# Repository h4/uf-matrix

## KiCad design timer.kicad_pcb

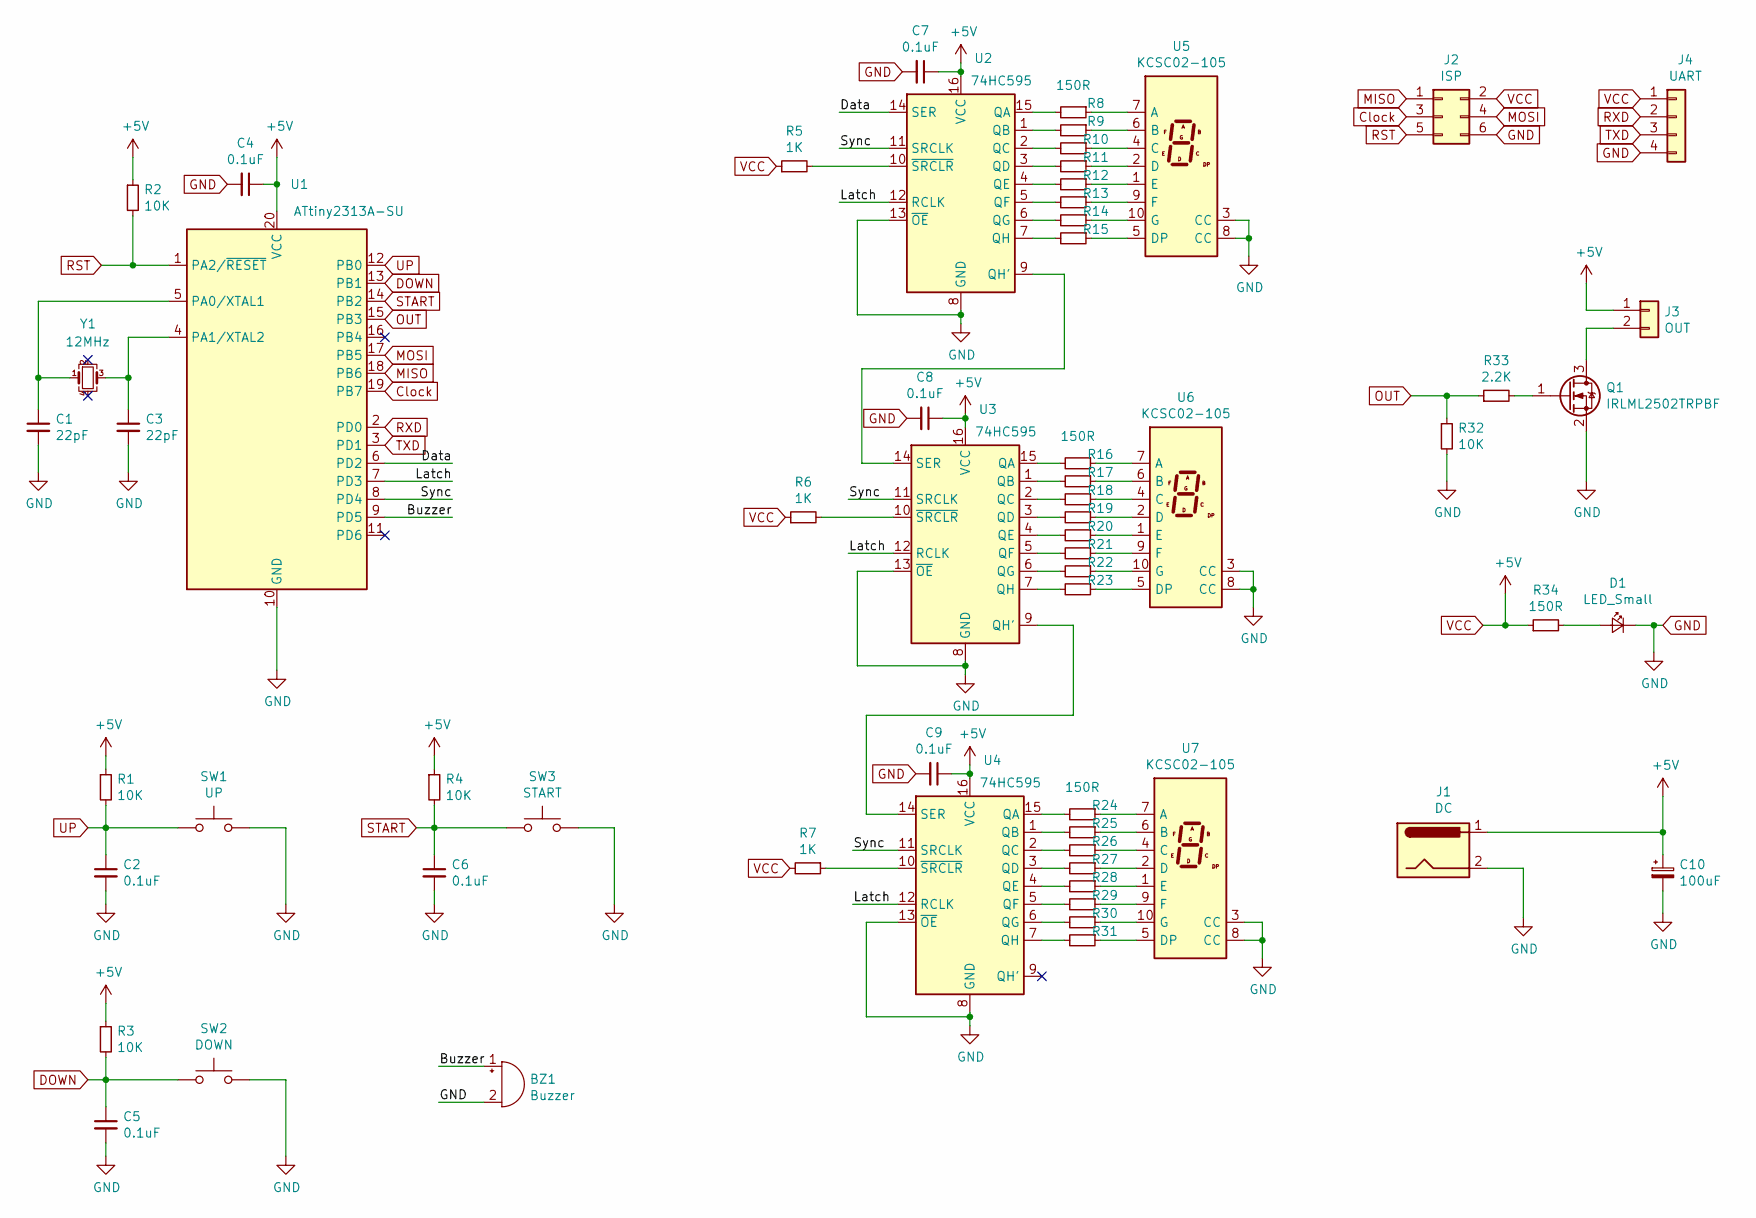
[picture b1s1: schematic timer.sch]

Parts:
BZ1: Buzzer; Buzzer_12x9.5RM7.6
C1, C3: 22pF; C_0805_2012Metric_Pad1.15x1.40mm_HandSolder
C2, C4, C5, C6, C7, C8, C9: 0.1uF; C_0805_2012Metric_Pad1.15x1.40mm_HandSolder
C10: 100uF; CP_EIA-7343-31_Kemet-D_Pad2.25x2.55mm_HandSolder
D1: LED_Small; LED_0805_2012Metric_Pad1.15x1.40mm_HandSolder
J1: DC; BarrelJack_Horizontal
J2: ISP; PinHeader_2x03_P2.54mm_Vertical
J3: OUT; TerminalBlock_TE_282834-2_1x02_P2.54mm_Horizontal
J4: UART; PinHeader_1x04_P2.54mm_Vertical
Q1: IRLML2502TRPBF; SOT-23
R1, R2, R3, R4, R32: 10K; R_0805_2012Metric_Pad1.15x1.40mm_HandSolder
R5, R6, R7: 1K; R_0805_2012Metric_Pad1.15x1.40mm_HandSolder
R8, R16, R24, R34: 150R; R_0805_2012Metric_Pad1.15x1.40mm_HandSolder
R9, R10, R11, R12, R13, R14, R15, R17, R18, R19, R20, R21, R22, R23, R25, R26, R27, R28, R29, R30, R31: R_Small; R_0805_2012Metric_Pad1.15x1.40mm_HandSolder
R33: 2.2K; R_0805_2012Metric_Pad1.15x1.40mm_HandSolder
SW1: UP; SW_SPST_EVPBF
SW2: DOWN; SW_SPST_EVPBF
SW3: START; SW_SPST_EVPBF
U1: ATtiny2313A-SU; SOIC-20W_7.5x12.8mm_P1.27mm
U2, U3, U4: 74HC595; SOIC-16_3.9x9.9mm_P1.27mm
U5, U6, U7: KCSC02-105
Y1: 12MHz; Crystal_SMD_SeikoEpson_FA238V-4Pin_3.2x2.5mm_HandSoldering

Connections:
/Buzzer: BZ1.1 (-), U1.9 (PD5)
/Data: U1.6 (PD2), U2.14 (SER)
/Latch: U1.7 (PD3), U2.12 (RCLK), U3.12 (RCLK), U4.12 (RCLK)
/Sync: U1.8 (PD4), U2.11 (SRCLK), U3.11 (SRCLK), U4.11 (SRCLK)
Clock: J2.3, U1.19 (PB7)
DOWN: C5.1, R3.2, SW2.1, U1.13 (PB1)
GND: BZ1.2 (+), C1.2, C2.2, C3.2, C4.2, C5.2, C6.2, C7.2, C8.2, C9.2, C10.2, D1.1 (K), J1.2, J2.6, J4.4, Q1.2 (S), R32.2, SW1.2, SW2.2, SW3.2, U1.10 (GND), U2.8 (GND), U2.13 (~OE), U3.8 (GND), U3.13 (~OE), U4.8 (GND), U4.13 (~OE), U5.3 (CC), U5.8 (CC), U6.3 (CC), U6.8 (CC), U7.3 (CC), U7.8 (CC)
MISO: J2.1, U1.18 (PB6)
MOSI: J2.4, U1.17 (PB5)
unnamed: C1.1, U1.5 (PA0/XTAL1), Y1.1
unnamed: C3.1, U1.4 (PA1/XTAL2), Y1.3
unnamed: D1.2 (A), R34.2
unnamed: J3.2, Q1.3 (D)
unnamed: Q1.1 (G), R33.2
unnamed: R5.2, U2.10 (~SRCLR)
unnamed: R6.2, U3.10 (~SRCLR)
unnamed: R7.1, U4.10 (~SRCLR)
unnamed: R8.1, U5.7 (A)
unnamed: R8.2, U2.15 (QA)
unnamed: R9.1, U5.6 (B)
unnamed: R9.2, U2.1 (QB)
unnamed: R10.1, U5.4 (C)
unnamed: R10.2, U2.2 (QC)
unnamed: R11.1, U5.2 (D)
unnamed: R11.2, U2.3 (QD)
unnamed: R12.1, U5.1 (E)
unnamed: R12.2, U2.4 (QE)
unnamed: R13.1, U5.9 (F)
unnamed: R13.2, U2.5 (QF)
unnamed: R14.1, U5.10 (G)
unnamed: R14.2, U2.6 (QG)
unnamed: R15.1, U5.5 (DP)
unnamed: R15.2, U2.7 (QH)
unnamed: R16.1, U6.7 (A)
unnamed: R16.2, U3.15 (QA)
unnamed: R17.1, U6.6 (B)
unnamed: R17.2, U3.1 (QB)
unnamed: R18.1, U6.4 (C)
unnamed: R18.2, U3.2 (QC)
unnamed: R19.1, U6.2 (D)
unnamed: R19.2, U3.3 (QD)
unnamed: R20.1, U6.1 (E)
unnamed: R20.2, U3.4 (QE)
unnamed: R21.1, U6.9 (F)
unnamed: R21.2, U3.5 (QF)
unnamed: R22.1, U6.10 (G)
unnamed: R22.2, U3.6 (QG)
unnamed: R23.1, U6.5 (DP)
unnamed: R23.2, U3.7 (QH)
unnamed: R24.1, U7.7 (A)
unnamed: R24.2, U4.15 (QA)
unnamed: R25.1, U7.6 (B)
unnamed: R25.2, U4.1 (QB)
unnamed: R26.1, U7.4 (C)
unnamed: R26.2, U4.2 (QC)
unnamed: R27.1, U7.2 (D)
unnamed: R27.2, U4.3 (QD)
unnamed: R28.1, U7.1 (E)
unnamed: R28.2, U4.4 (QE)
unnamed: R29.1, U7.9 (F)
unnamed: R29.2, U4.5 (QF)
unnamed: R30.1, U7.10 (G)
unnamed: R30.2, U4.6 (QG)
unnamed: R31.1, U7.5 (DP)
unnamed: R31.2, U4.7 (QH)
unnamed: U2.9 (QH'), U3.14 (SER)
unnamed: U3.9 (QH'), U4.14 (SER)
OUT: R32.1, R33.1, U1.15 (PB3)
RST: J2.5, R2.2, U1.1 (PA2/~RESET)
RXD: J4.2, U1.2 (PD0)
START: C6.1, R4.2, SW3.1, U1.14 (PB2)
TXD: J4.3, U1.3 (PD1)
UP: C2.1, R1.2, SW1.1, U1.12 (PB0)
VCC: C4.1, C7.1, C8.1, C9.1, C10.1, J1.1, J2.2, J3.1, J4.1, R1.1, R2.1, R3.1, R4.1, R5.1, R6.1, R7.2, R34.1, U1.20 (VCC), U2.16 (VCC), U3.16 (VCC), U4.16 (VCC)

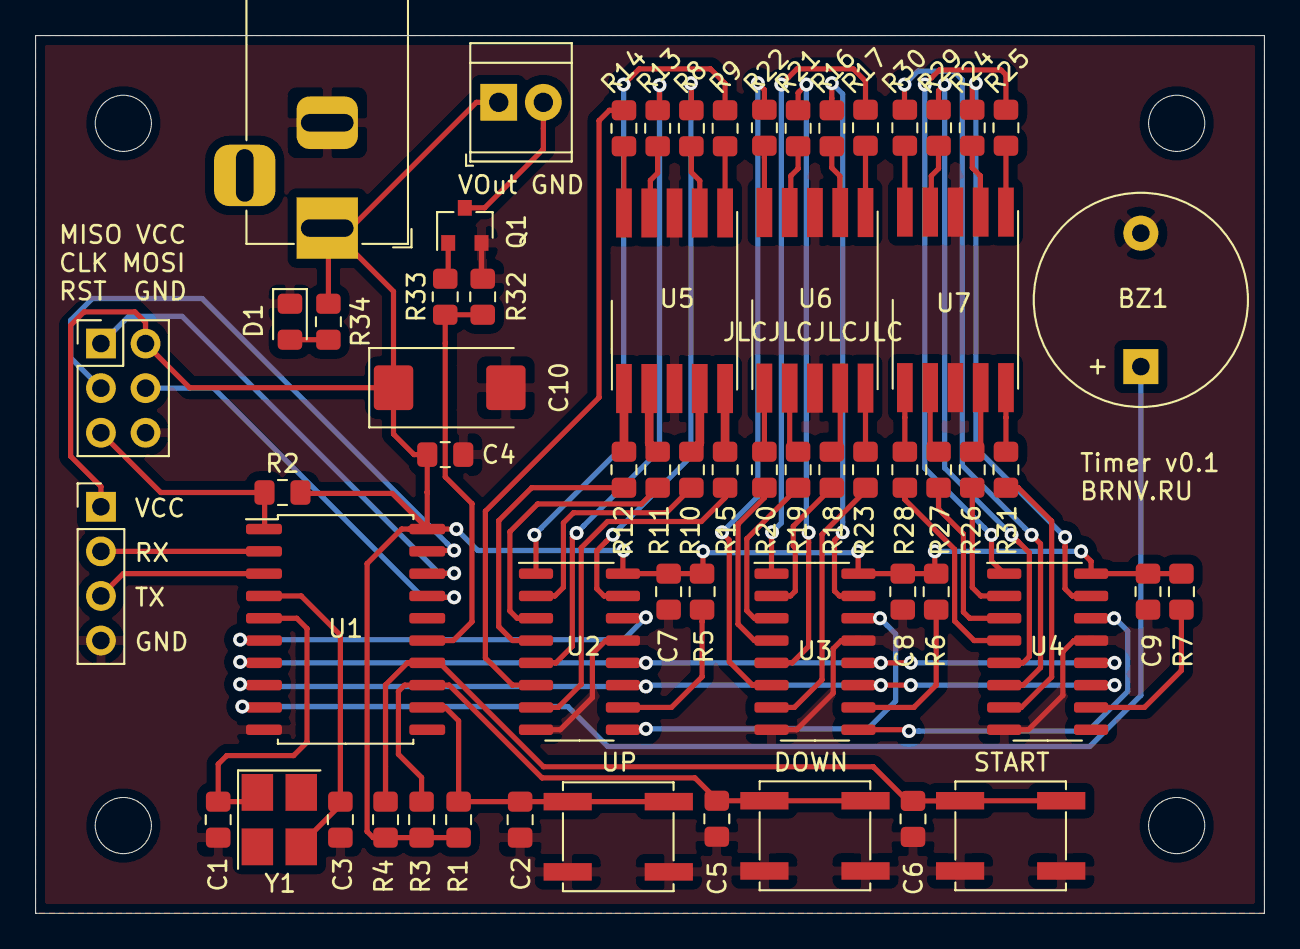
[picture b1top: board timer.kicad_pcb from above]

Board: 2 copper layers, 70.0 x 50.0 mm, 62 parts (0 on the bottom side), 74 nets.

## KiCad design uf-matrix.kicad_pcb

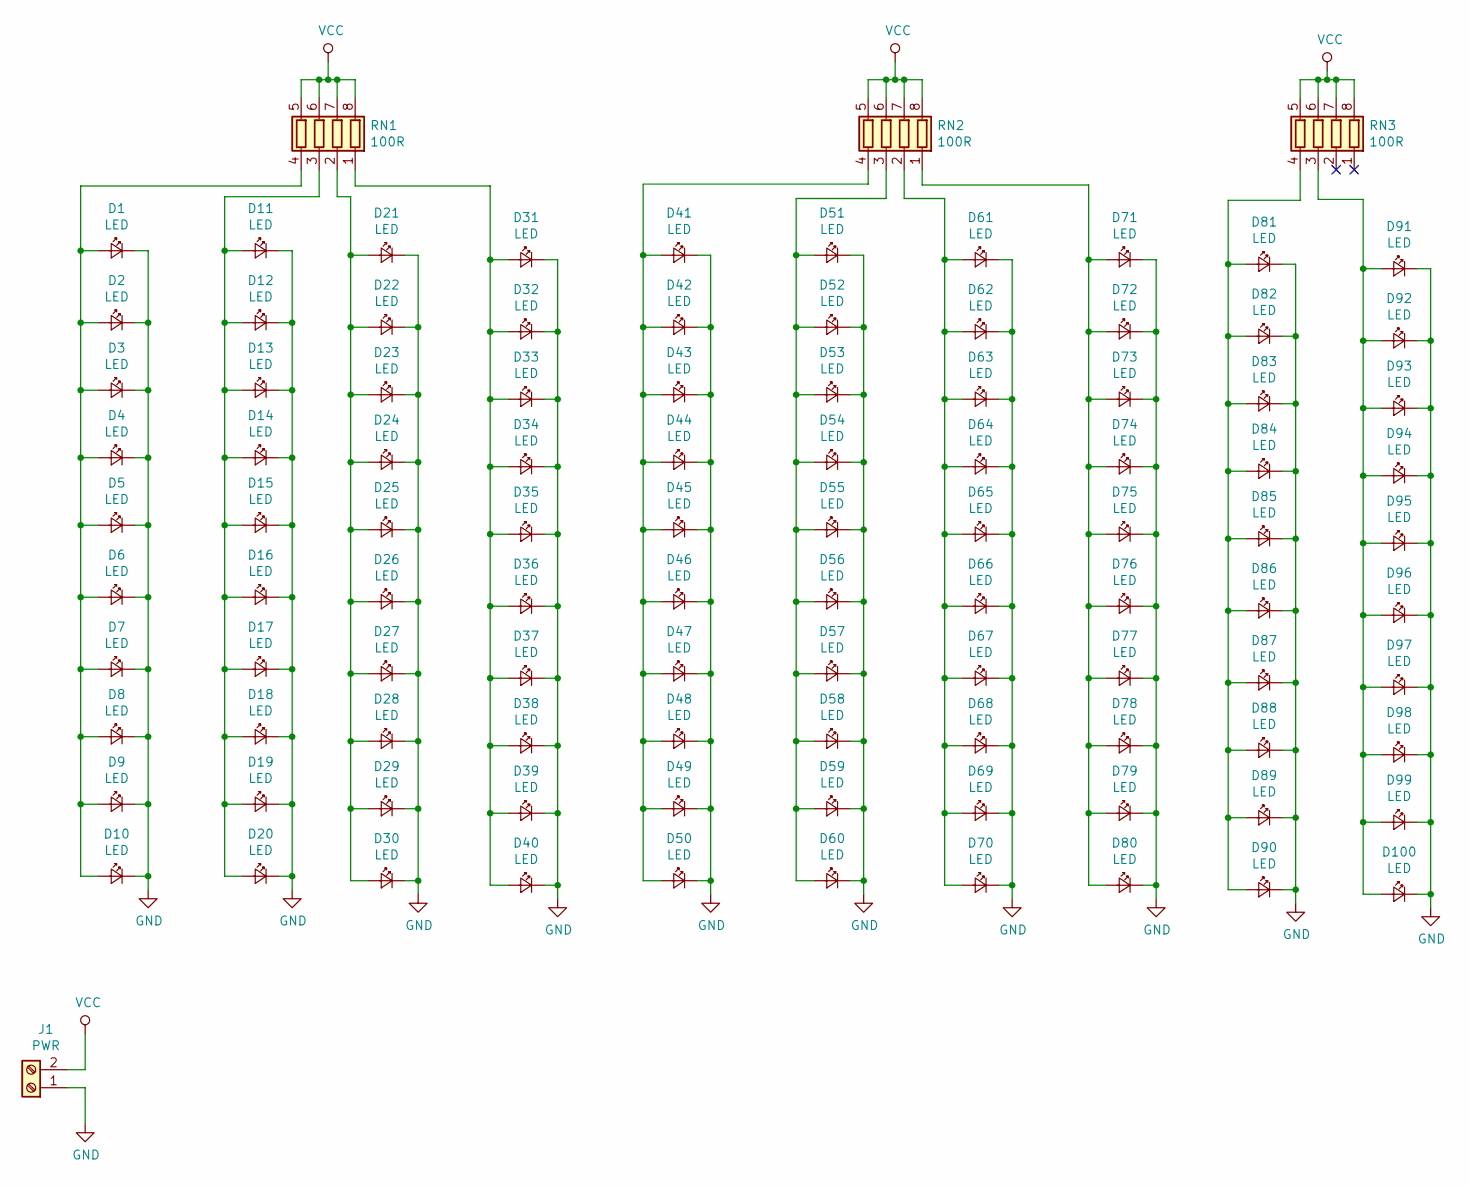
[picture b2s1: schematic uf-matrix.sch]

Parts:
D1, D2, D3, D4, D5, D6, D7, D8, D9, D10, D11, D12, D13, D14, D15, D16, D17, D18, D19, D20, D21, D22, D23, D24, D25, D26, D27, D28, D29, D30, D31, D32, D33, D34, D35, D36, D37, D38, D39, D40, D41, D42, D43, D44, D45, D46, D47, D48, D49, D50, D51, D52, D53, D54, D55, D56, D57, D58, D59, D60, D61, D62, D63, D64, D65, D66, D67, D68, D69, D70, D71, D72, D73, D74, D75, D76, D77, D78, D79, D80, D81, D82, D83, D84, D85, D86, D87, D88, D89, D90, D91, D92, D93, D94, D95, D96, D97, D98, D99, D100: LED; LED_1210_3225Metric_Pad1.42x2.65mm_HandSolder
J1: PWR; TerminalBlock_bornier-2_P5.08mm
RN1, RN2, RN3: 100R; R_Array_Convex_4x0603

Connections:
GND: D1.1 (K), D2.1 (K), D3.1 (K), D4.1 (K), D5.1 (K), D6.1 (K), D7.1 (K), D8.1 (K), D9.1 (K), D10.1 (K), D11.1 (K), D12.1 (K), D13.1 (K), D14.1 (K), D15.1 (K), D16.1 (K), D17.1 (K), D18.1 (K), D19.1 (K), D20.1 (K), D21.1 (K), D22.1 (K), D23.1 (K), D24.1 (K), D25.1 (K), D26.1 (K), D27.1 (K), D28.1 (K), D29.1 (K), D30.1 (K), D31.1 (K), D32.1 (K), D33.1 (K), D34.1 (K), D35.1 (K), D36.1 (K), D37.1 (K), D38.1 (K), D39.1 (K), D40.1 (K), D41.1 (K), D42.1 (K), D43.1 (K), D44.1 (K), D45.1 (K), D46.1 (K), D47.1 (K), D48.1 (K), D49.1 (K), D50.1 (K), D51.1 (K), D52.1 (K), D53.1 (K), D54.1 (K), D55.1 (K), D56.1 (K), D57.1 (K), D58.1 (K), D59.1 (K), D60.1 (K), D61.1 (K), D62.1 (K), D63.1 (K), D64.1 (K), D65.1 (K), D66.1 (K), D67.1 (K), D68.1 (K), D69.1 (K), D70.1 (K), D71.1 (K), D72.1 (K), D73.1 (K), D74.1 (K), D75.1 (K), D76.1 (K), D77.1 (K), D78.1 (K), D79.1 (K), D80.1 (K), D81.1 (K), D82.1 (K), D83.1 (K), D84.1 (K), D85.1 (K), D86.1 (K), D87.1 (K), D88.1 (K), D89.1 (K), D90.1 (K), D91.1 (K), D92.1 (K), D93.1 (K), D94.1 (K), D95.1 (K), D96.1 (K), D97.1 (K), D98.1 (K), D99.1 (K), D100.1 (K), J1.1
unnamed: D1.2 (A), D2.2 (A), D3.2 (A), D4.2 (A), D5.2 (A), D6.2 (A), D7.2 (A), D8.2 (A), D9.2 (A), D10.2 (A), RN1.4 (R4.1)
unnamed: D11.2 (A), D12.2 (A), D13.2 (A), D14.2 (A), D15.2 (A), D16.2 (A), D17.2 (A), D18.2 (A), D19.2 (A), D20.2 (A), RN1.3 (R3.1)
unnamed: D21.2 (A), D22.2 (A), D23.2 (A), D24.2 (A), D25.2 (A), D26.2 (A), D27.2 (A), D28.2 (A), D29.2 (A), D30.2 (A), RN1.2 (R2.1)
unnamed: D31.2 (A), D32.2 (A), D33.2 (A), D34.2 (A), D35.2 (A), D36.2 (A), D37.2 (A), D38.2 (A), D39.2 (A), D40.2 (A), RN1.1 (R1.1)
unnamed: D41.2 (A), D42.2 (A), D43.2 (A), D44.2 (A), D45.2 (A), D46.2 (A), D47.2 (A), D48.2 (A), D49.2 (A), D50.2 (A), RN2.4 (R4.1)
unnamed: D51.2 (A), D52.2 (A), D53.2 (A), D54.2 (A), D55.2 (A), D56.2 (A), D57.2 (A), D58.2 (A), D59.2 (A), D60.2 (A), RN2.3 (R3.1)
unnamed: D61.2 (A), D62.2 (A), D63.2 (A), D64.2 (A), D65.2 (A), D66.2 (A), D67.2 (A), D68.2 (A), D69.2 (A), D70.2 (A), RN2.2 (R2.1)
unnamed: D71.2 (A), D72.2 (A), D73.2 (A), D74.2 (A), D75.2 (A), D76.2 (A), D77.2 (A), D78.2 (A), D79.2 (A), D80.2 (A), RN2.1 (R1.1)
unnamed: D81.2 (A), D82.2 (A), D83.2 (A), D84.2 (A), D85.2 (A), D86.2 (A), D87.2 (A), D88.2 (A), D89.2 (A), D90.2 (A), RN3.4 (R4.1)
unnamed: D91.2 (A), D92.2 (A), D93.2 (A), D94.2 (A), D95.2 (A), D96.2 (A), D97.2 (A), D98.2 (A), D99.2 (A), D100.2 (A), RN3.3 (R3.1)
VCC: J1.2, RN1.5 (R4.2), RN1.6 (R3.2), RN1.7 (R2.2), RN1.8 (R1.2), RN2.5 (R4.2), RN2.6 (R3.2), RN2.7 (R2.2), RN2.8 (R1.2), RN3.5 (R4.2), RN3.6 (R3.2), RN3.7 (R2.2), RN3.8 (R1.2)

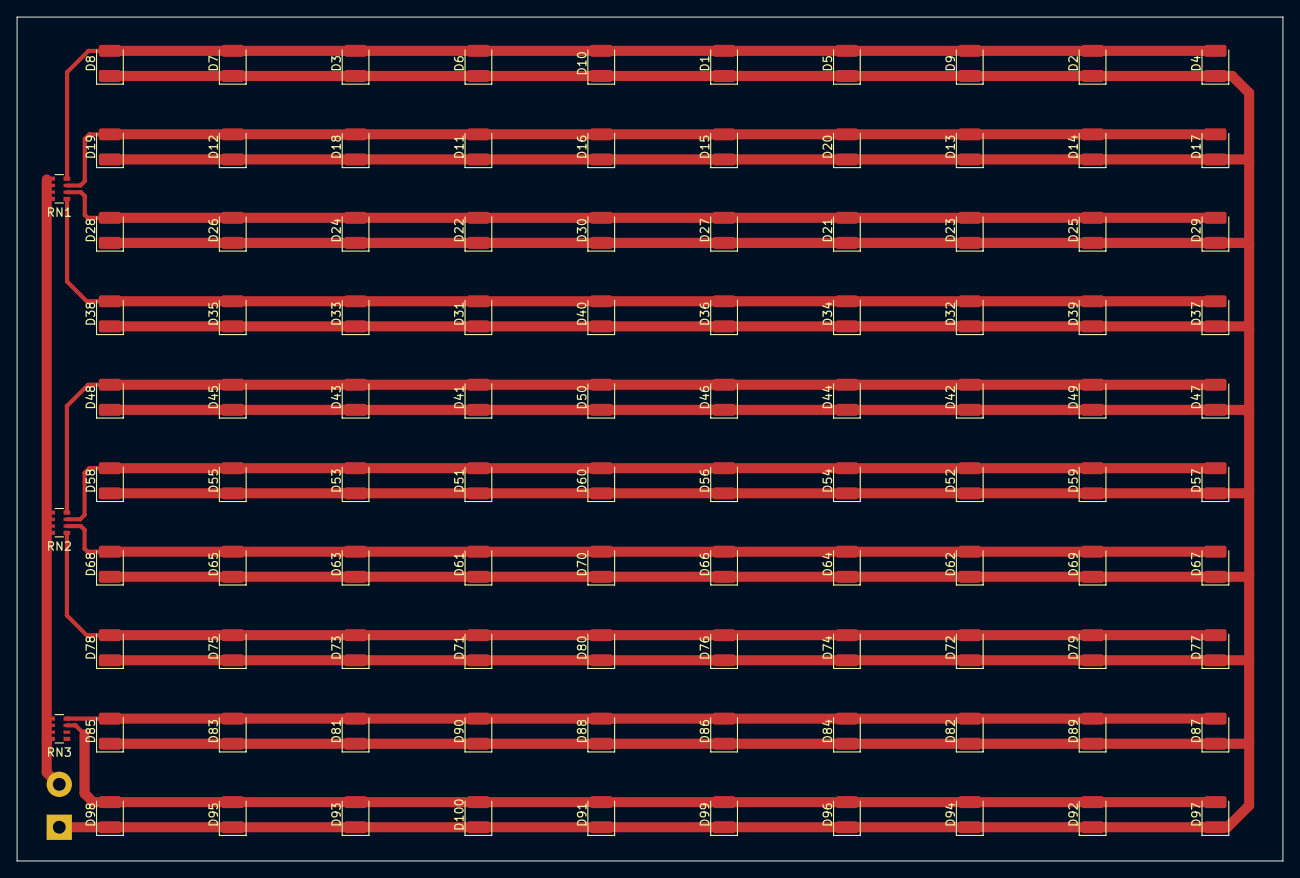
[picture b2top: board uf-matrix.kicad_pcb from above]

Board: 2 copper layers, 150.0 x 100.0 mm, 104 parts (1 on the bottom side), 12 nets.

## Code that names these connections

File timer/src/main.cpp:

#include <Arduino.h>
#include <avr/io.h>
#include <util/delay.h>

#define OUT_PIN PB3
#define DATA_PIN PD2
#define LATCH_PIN PD3
#define CLOCK_PIN PD4
#define BUZZER_PIN PD5

#define UP_PIN PB0
#define DOWN_PIN PB1
#define START_PIN PB2

bool state = false;
unsigned int time = 45;
unsigned int elapsed;
bool timer_enabled = false;

unsigned int NUMS_MAP[10] = {
    //abcdefg.
    0b00111111,
    0b00000110,
    0b01011011,
    0b01001111,
    0b01100110,
    0b01101101,
    0b01111101,
    0b00000111,
    0b01111111,
    0b01101111
};

void pinHigh(volatile uint8_t *port, int pin) {
  *port |= (1 << pin);
}

void pinLow(volatile uint8_t *port, int pin) {
  *port &= ~(1 << pin);
}

void init_led() {
  DDRD |= ((1 << DATA_PIN) | (1 << CLOCK_PIN) | (1 << LATCH_PIN));
}

void init_buzzer() {
  DDRD |= (1 << BUZZER_PIN);
  // Configure counter for PWM. Enable PWM, set fast PWM, use external crystal
  TCCR0A = (1 << COM0A1) | (1 << COM0B1) | (1 << WGM01) | (1 << WGM00) | (1 << CS02) | (1 << CS01) | (1 << CS00);
}

void init_buttons() {
  DDRB &= (~(1 << UP_PIN) & ~(1 << DOWN_PIN) & ~(1 << START_PIN));
  PORTB |= ((1 << START_PIN) | (1 << DOWN_PIN) | (1 << START_PIN));
}

void init_out() {
  DDRB |= (1 << OUT_PIN);
  PORTB &= ~(1 << OUT_PIN);
}

void setup() {
  PORTB = 0b00000000;
  
  init_buttons();
  init_led();
  init_buzzer();
  init_out();
}

void put_byte(int n, bool invert) {
  int bits = NUMS_MAP[n];
  if (invert) {
    bits = ~bits;
  }

  for (int i=0; i < 8; i++) {
    //Output the data on DS line according to the
    //Value of MSB
    if (bits & 0b10000000) {
        //MSB is 1 so output high
        pinHigh(&PORTD, DATA_PIN);
    } else {
        //MSB is 0 so output high
        pinLow(&PORTD, DATA_PIN);
    }
    pinHigh(&PORTD, CLOCK_PIN);
    pinLow(&PORTD, CLOCK_PIN);
    bits = bits << 1;  //Now bring ne0t bit at MSB position
  }
}

void swow_number(int n) {

  pinLow(&PORTD, LATCH_PIN);

  put_byte(n % 10, false);
  put_byte(n / 10, false);
  put_byte(n / 100, false);
  //Now all 8 bits have been transferred to shift register
  //Move them to output latch at one
  pinHigh(&PORTD, LATCH_PIN);
}

bool button_up_pressed() {
  return (PINB & (1 << UP_PIN)) == 0;
}

bool button_down_pressed() {
  return (PINB & (1 << DOWN_PIN)) == 0;
}

bool button_start_pressed() {
  return (PINB & (1 << START_PIN)) == 0;
}

void inc_time() {
  if (time < 99) {
    time++;
  }
}

void dec_time() {
  if (time > 0) {
    time--;
  }
}

const int Note_C  = 239;
const int Note_CS = 225;
const int Note_D  = 213;
const int Note_DS = 201;
const int Note_E  = 190;
const int Note_F  = 179;
const int Note_FS = 169;
const int Note_G  = 159;
const int Note_GS = 150;
const int Note_A  = 142;
const int Note_AS = 134;
const int Note_B  = 127;

void TinyTone(unsigned char divisor, unsigned char octave, unsigned long duration)
{
  // Start PWM output
  TCCR0B = (1 << CS01); 
  OCR0B  = divisor-1;
  delay(duration);
  // Stop PWM output
  TCCR0B = 0x90;
}

void tick() {
  if (elapsed > 0) {
    elapsed--;
  } else {
    timer_enabled = false;
    pinLow(&PORTB, OUT_PIN);
    TinyTone(Note_A, 4, 2000);
    TinyTone(Note_G, 4, 2000);
    TinyTone(Note_F, 4, 2000);
    TinyTone(Note_E, 4, 2000);
    TinyTone(Note_D, 4, 2000);
  }

  swow_number(elapsed);
  _delay_ms(1000);
}

void loop() {
  if (timer_enabled) {
    tick();
  } else {
    if (button_up_pressed()) {
      inc_time();
    }
    if (button_down_pressed()) {
      dec_time();
    }
    if (button_start_pressed()) {
        timer_enabled = true;
        elapsed = time;
        pinHigh(&PORTB, OUT_PIN);
    }
    
    swow_number(time);
    _delay_ms(200);
  }

}

int main(void) {
  setup();

  while(1) {
    loop();
  }
}
